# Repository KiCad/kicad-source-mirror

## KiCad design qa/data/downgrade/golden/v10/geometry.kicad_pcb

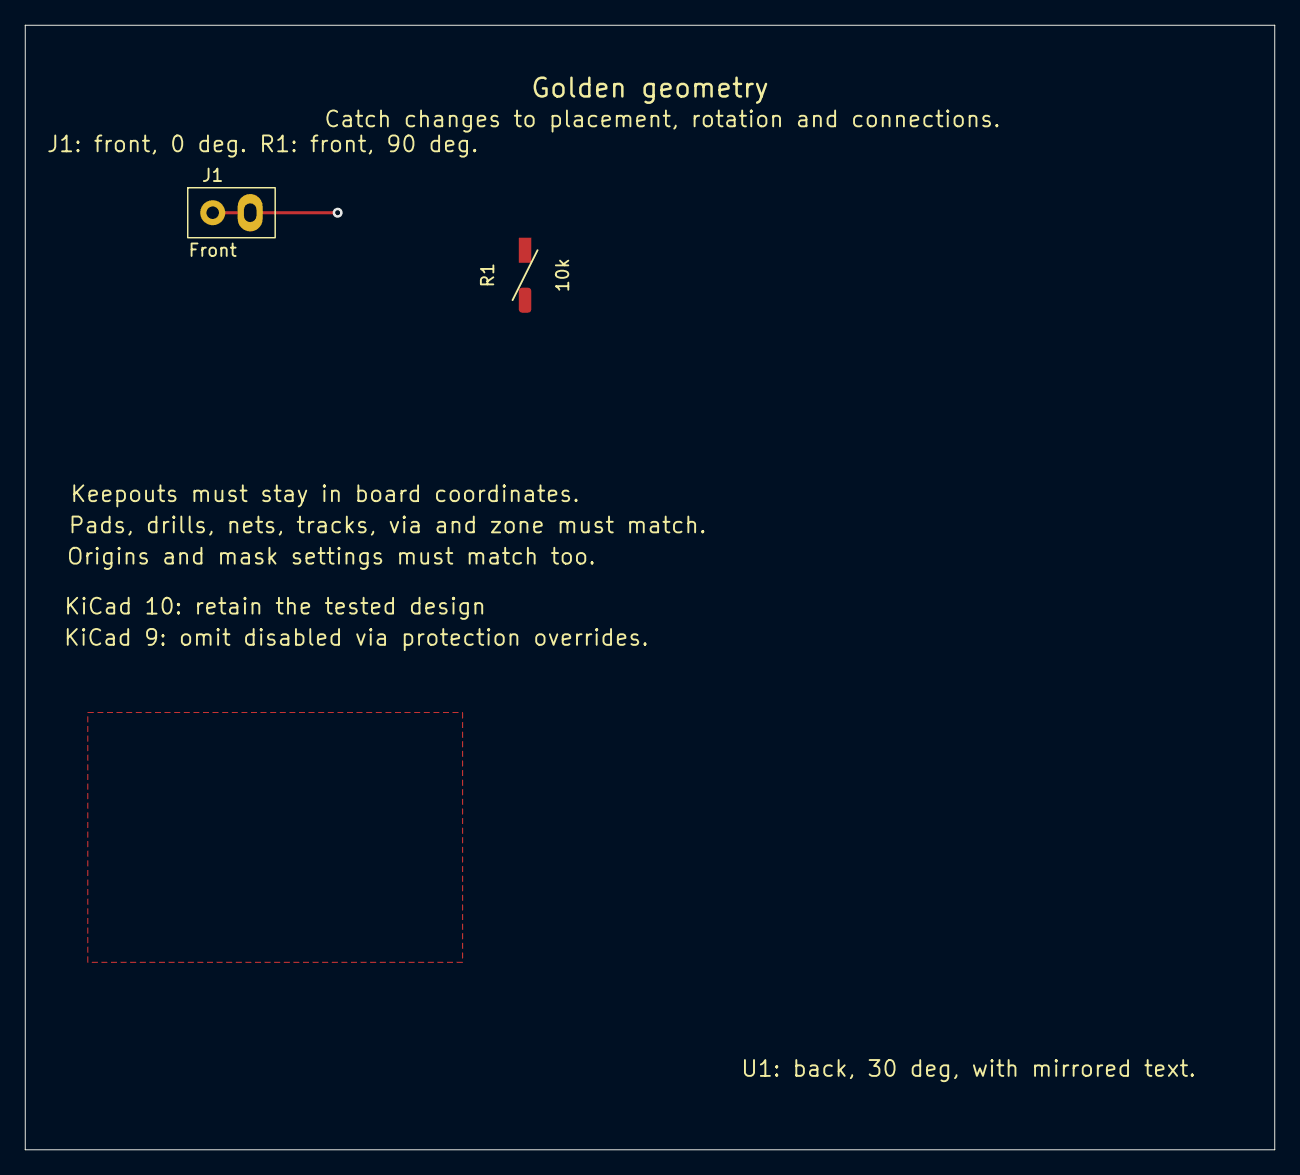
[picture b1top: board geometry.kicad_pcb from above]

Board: 2 copper layers, 100.0 x 90.0 mm, 3 parts (1 on the bottom side), 2 nets.

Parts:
J1: Front
R1: 10k; RotatedFront
U1: Back

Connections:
GND: J1.2, R1.2, U1.2
SIGNAL: J1.1, R1.1, U1.1
